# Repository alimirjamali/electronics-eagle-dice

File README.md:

# A small 1 Inch square Dice
This is a simple dice design using Microchip PIC12F1822 microcontroller.

## Notes
There is no any space left on the PCB for ICSP header.
Microcontrollers are programmed via a SOIC to DIP adapter and then are soldered to dice PCBs.
I am currently using another Microchip MCU (12F1822) rather than PIC12F629 used in the original design.

## Schematic

## PCB (without copper pour)

## Assembled dice (Rev 1)

# Credits
This project is more or less based on [Colin Mitchell's article](http://www.talkingelectronics.com/projects/LED%20Dice%20with%20PIC/Dice.html) for [Talking Electronics](https://en.wikipedia.org/wiki/Talking_Electronics) magazine. 

# To do
It would be much better to keep the PIC always powered on but in Sleep mode or Watchdog timer.
After switch is pressed, PIC should resume normal operation and roll the dice.
Then it could switch back to Sleep mode one minute after showing the result.
I have to study PIC12F1822 documentation to learn how to use it's Sleep mode.

# License
This hardware is licensed under [Creative Commons Share Alike](http://creativecommons.org/licenses/by-sa/4.0/).

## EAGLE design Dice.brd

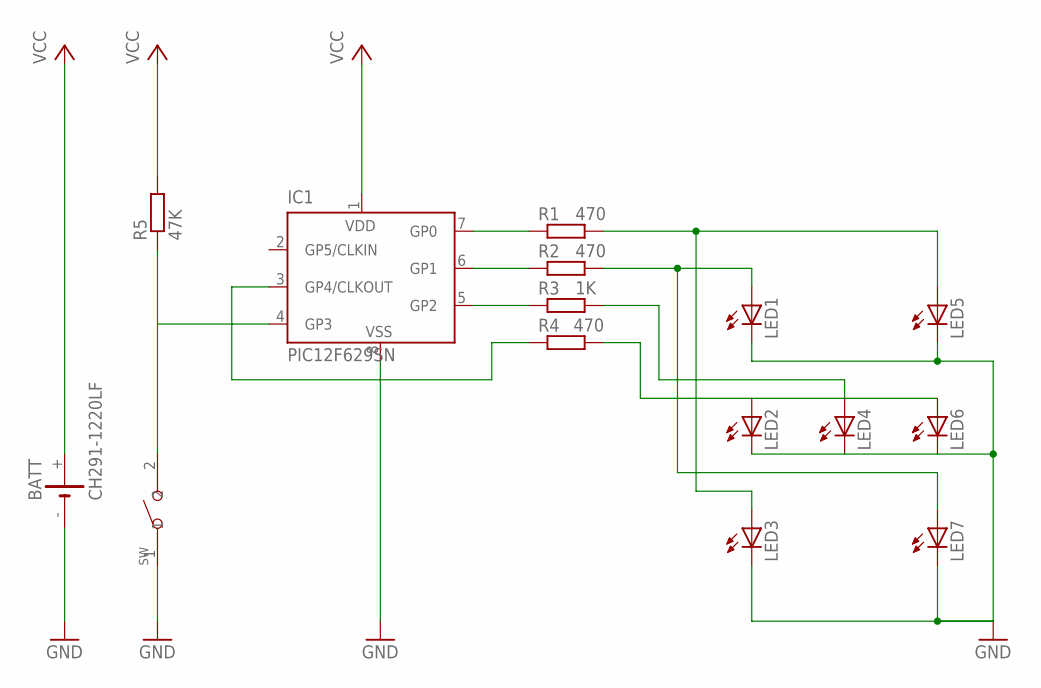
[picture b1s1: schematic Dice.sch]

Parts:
BATT: CH291-1220LF
IC1: PIC12F629SN; SO-08
LED1, LED2, LED3, LED4, LED5, LED6, LED7: LEDCHIPLED_0805; CHIPLED_0805
R1, R2, R4: 470; R0805
R3: 1K; R0805
R5: 47K; R0805
SW: SMD-BUTTON(2P-6.0X3.0X2.5MM)-DHT-1163S; SW2-4.0-6.0X3.0X2.5MM

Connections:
GND: BATT.-, IC1.8 (VSS), LED1.C, LED2.C, LED3.C, LED4.C, LED5.C, LED6.C, LED7.C, SW.1
GP0: IC1.7 (GP0), R1.1
GP1: IC1.6 (GP1), R2.1
GP2: IC1.5 (GP2), R3.1
GP3: IC1.4 (GP3), R5.1, SW.2
GP4: IC1.3 (GP4/CLKOUT), R4.1
LED1&7: LED1.A, LED7.A, R2.2
LED2&6: LED2.A, LED6.A, R4.2
LED3&5: LED3.A, LED5.A, R1.2
LED4: LED4.A, R3.2
VCC: BATT.+, IC1.1 (VDD), R5.2

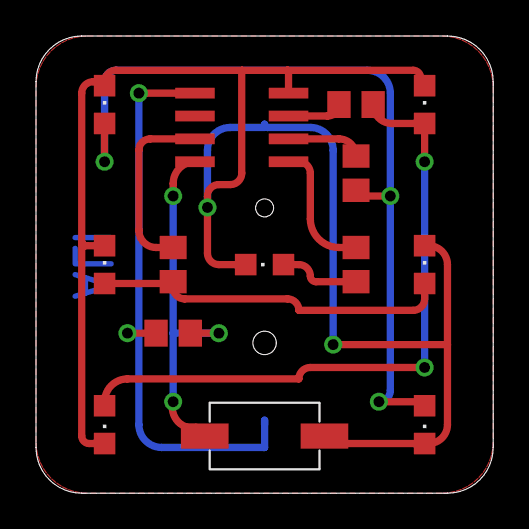
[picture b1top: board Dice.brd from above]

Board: 2 copper layers, 25.4 x 25.4 mm, 15 parts (1 on the bottom side), 11 nets.

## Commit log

2017-03-02 Altium PCB
2017-03-02 Crediting Talking Electronics article
2017-03-08 Adding copper pour
2017-03-08 Finished board in action
2017-03-08 Always powered
2017-03-13 Revision 2
2017-03-13 Correcting Eagle Description File
